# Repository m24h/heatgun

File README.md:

# heatgun
A small hot air station for soldering, using type-858 heat gun as handle, STC8G1k17 as MCU, copper wire resistor for cold junction compensation.

##Features:

* Small, cheap, esay to make
* With cold junction compensation
* Software correction 
* Compatible with most type-858 handle
* Settings can be remembered
* PID temperature control

## Burning/Downloading

This program is only for MCU STC8G1K17-16pin, compiled and linked by SDCC 4.2.0

It must be burned at following scheme:

* Internal IRC Freq. : 22.1184MHz (as same as specified in def.h)
* User EEPROM size : 2k (as same as specified in def.h)
* Low-voltage reset : Enable
* Reset pin used as I/O port : Yes
* Hardware enable WDT : Disable (I will use software enable it)
* Add a reset code in front of ID : Yes (it will adds Band-Gap voltage reference)
* Erase all EEPROM data : Yes
* Fill data to space area : 0XFF

## About cold junction compensation for the thermocouple in the handle

I add a coper wire wound resistor (nearly 13.5 OHM) in the handle, in series with the thermocouple, for cold junction compensation at a suitable bias current.
And my software will do some corrections/calculations for getting accurate temperature from the thermocouple.

But if the connector between your handle and main controller board is not in good contact, this will introduce jitter in the temperature values.

In this case, the coper wire resistor can be totally removed, and several components (R5,R13) on the PCB can also be removed,
and several parameters inside the program can also be adjusted (set g_ana_pk=0 at main.c). 

In fact, the temperature rising of the thermocouple's cold junction within the handle, is not obvious. 
It is not really necessary to do cold junction compensation, and there are already an offset compensation. 
As long as you press and hold the button at startup, you can enter room temperature parameter.
In most cases, this is enough.

## About offset adjustment for AMP (LM321)

LM321 used in my circuit is not a precision OP-AMP and there may be large input offset voltage (normally within a few millivolts).
Because of the cold junction compensation circuit, its negative offset can be ignored, 
but if the positive offset is too large, it may be necessary to add resistor (R14) to the circuit for keeping the output in the linear range.

If you remove the cold junction compensation resistor in the handle, and the negative offset cannot be ignored, 
I suggest that you still need to add one resistor in series, however, this resistor can take a larger value, 
and at the same time increase the values of R5 and R13 in the circuit, 
so that there will be no obvious jitter caused by the connector contact resistor.

Also do not adjust the offset to 0, keep an output of OP-AMP hundreds of millivolts at least.

## About the gain of AMP (LM321)

LM321 is also not a rail-to-rail OP-AMP, especially since its high output is close to 1V away from the power voltage.

If the gain designed is too large, the temperature measurement range will be limited. 
With my current design, there is no problem with the range within 500 centidegrees, 
but if a larger range is needed, the gain needs to be reduced (change R8/R9) and the parameters (g_ana_gain at main.c) in program needs to be adjusted too.

## About power supply

The circuit requires 2 ways of power supply, a 5V for controller, another 24V for the fan (normally 24V 0.1xxA) in the handle.
I didn't include this in my design, you can use the finished product from other way, or modify an unused phone charger like me (10W required).

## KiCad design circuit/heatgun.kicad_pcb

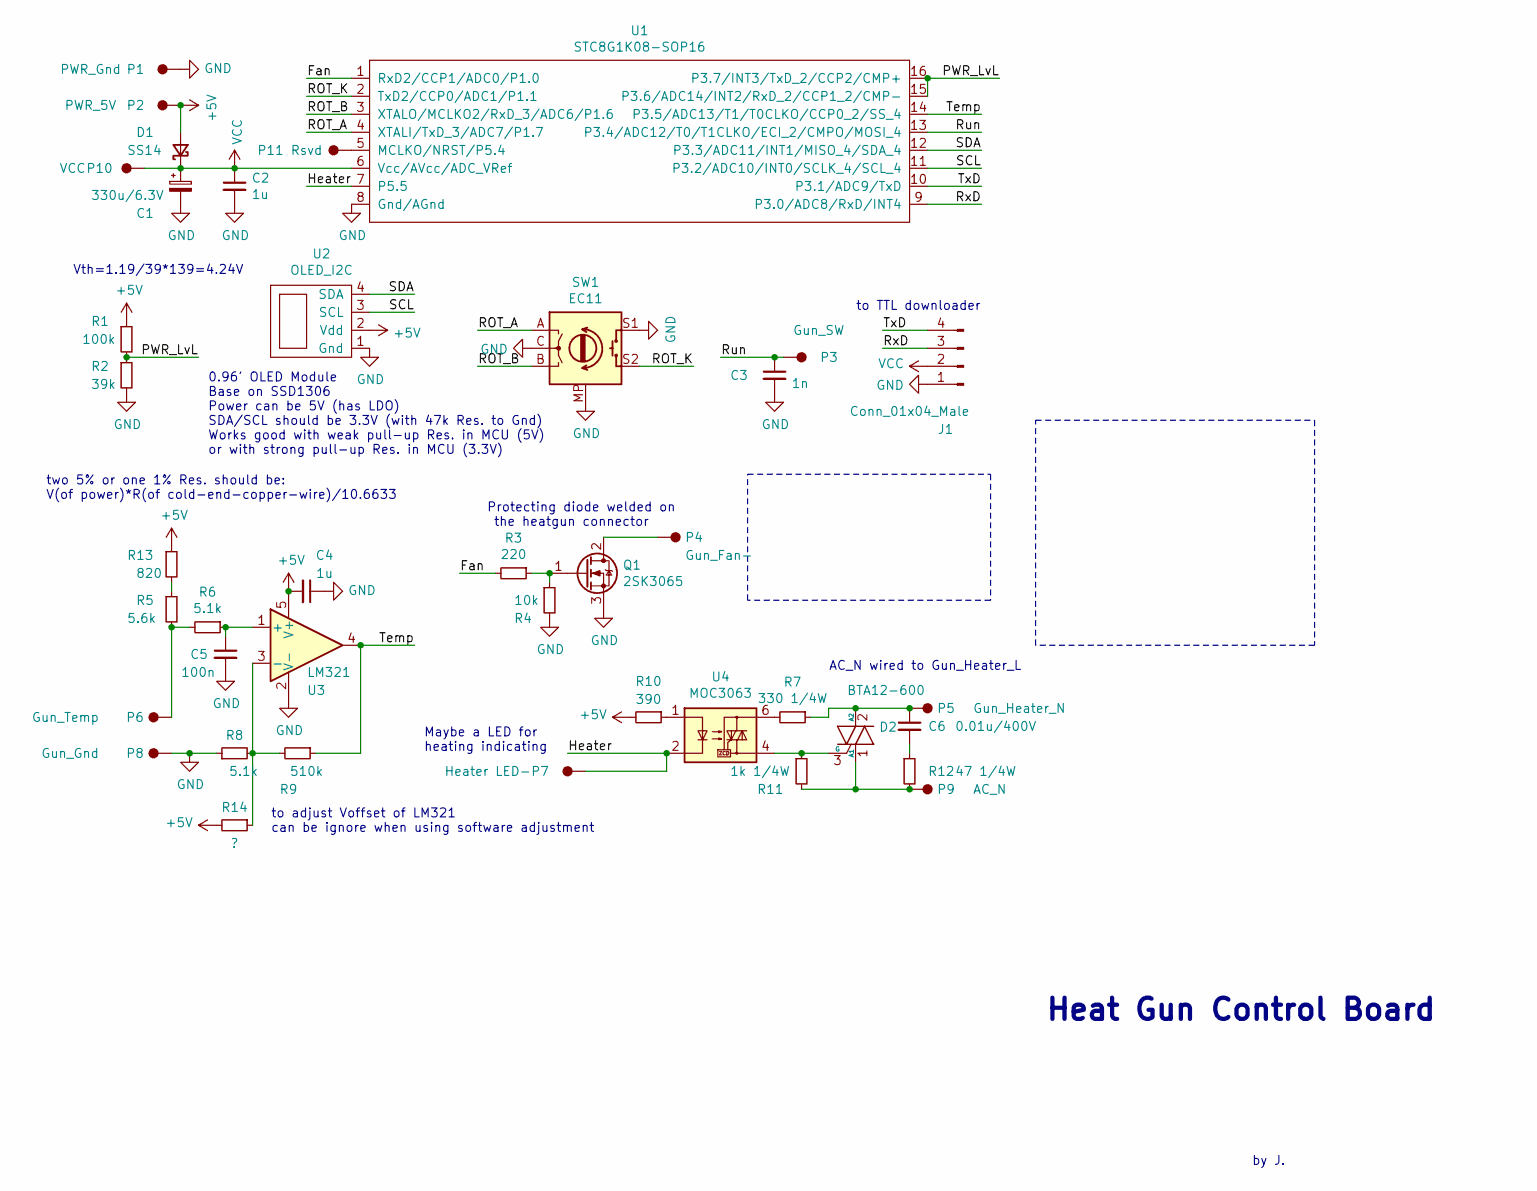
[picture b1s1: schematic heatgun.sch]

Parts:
C1: 330u/6.3V; CP_Radial_D8.0mm_P5.00mm
C2, C4: 1u; C_0603_1608Metric
C3: 1n; C_0603_1608Metric
C5: 100n; C_0603_1608Metric
C6: 0.01u/400V; C_Rect_L7.0mm_W2.5mm_P5.00mm
D1: SS14; D_SMA
D2: BTA12-600; TO-220-3_Vertical
J1: Conn_01x04_Male; PinHeader_1x04_P2.54mm_Vertical
P1: PWR_Gnd; Pad-1.8-h1
P2: PWR_5V; Pad-1.8-h1
P3: Gun_SW; Pad-1.8-h1
P4: Gun_Fan-; Pad-1.8-h1
P5: Gun_Heater_N; Pad-2.5-h1
P6: Gun_Temp; Pad-1.8-h1
P7: Heater LED-; Pad-1.8-h1
P8: Gun_Gnd; Pad-1.8-h1
P9: AC_N; Pad-2.5-h1
P10: VCC; Pad-1.8-h1
P11: Rsvd; Pad-1.8-h1
Q1: 2SK3065; SOT-89-3
R1: 100k; R_0603_1608Metric
R2: 39k; R_0603_1608Metric
R3: 220; R_0603_1608Metric
R4: 10k; R_0603_1608Metric
R5: 5.6k; R_0603_1608Metric
R6, R8: 5.1k; R_0603_1608Metric
R7: 330 1/4W; R_Axial_DIN0207_L6.3mm_D2.5mm_P10.16mm_Horizontal
R9: 510k; R_0603_1608Metric
R10: 390; R_Axial_DIN0207_L6.3mm_D2.5mm_P10.16mm_Horizontal
R11: 1k 1/4W; R_Axial_DIN0207_L6.3mm_D2.5mm_P10.16mm_Horizontal
R12: 47 1/4W; R_Axial_DIN0207_L6.3mm_D2.5mm_P10.16mm_Horizontal
R13: 820; R_0603_1608Metric
R14: ?; R_0603_1608Metric
SW1: EC11; RotaryEncoder_Alps_EC11E-Switch_Vertical_H20mm
U1: STC8G1K08-SOP16; SOIC-16_3.9x9.9mm_P1.27mm
U2: OLED_I2C; OLED-I2C-0.96-27.5X27.8
U3: LM321; SOT-23-5
U4: MOC3063; DIP-6_W7.62mm

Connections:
+5V: C4.2, D1.2 (A), P2.1, R1.1, R10.2, R13.1, R14.2, U2.2 (Vdd), U3.5 (V+)
/Fan: R3.2, U1.1 (RxD2/CCP1/ADC0/P1.0)
/Heater: P7.1, U1.7 (P5.5), U4.2
/PWR_LvL: R1.2, R2.1, U1.15 (P3.6/ADC14/INT2/RxD_2/CCP1_2/CMP-), U1.16 (P3.7/INT3/TxD_2/CCP2/CMP+)
/ROT_A: SW1.A, U1.4 (XTALI/TxD_3/ADC7/P1.7)
/ROT_B: SW1.B, U1.3 (XTALO/MCLKO2/RxD_3/ADC6/P1.6)
/ROT_K: SW1.S2, U1.2 (TxD2/CCP0/ADC1/P1.1)
/Run: C3.1, P3.1, U1.13 (P3.4/ADC12/T0/T1CLKO/ECI_2/CMPO/MOSI_4)
/RxD: J1.3, U1.9 (P3.0/ADC8/RxD/INT4)
/SCL: U1.11 (P3.2/ADC10/INT0/SCLK_4/SCL_4), U2.3 (SCL)
/SDA: U1.12 (P3.3/ADC11/INT1/MISO_4/SDA_4), U2.4 (SDA)
/Temp: R9.1, U1.14 (P3.5/ADC13/T1/T0CLKO/CCP0_2/SS_4), U3.4
/TxD: J1.4, U1.10 (P3.1/ADC9/TxD)
GND: C1.2, C2.2, C3.2, C4.1, C5.2, J1.1, P1.1, P8.1, Q1.3 (S), R2.2, R4.2, R8.1, SW1.C, SW1.MP, SW1.S1, U1.8 (Gnd/AGnd), U2.1 (Gnd), U3.2 (V-)
unnamed: C5.1, R6.1, U3.1 (+)
unnamed: C6.1, D2.2 (A2), P5.1, R7.1
unnamed: C6.2, R12.1
unnamed: D2.1 (A1), P9.1, R11.2, R12.2
unnamed: D2.3 (G), R11.1, U4.4
unnamed: P4.1, Q1.2 (D)
unnamed: P6.1, R5.2, R6.2
unnamed: P11.1, U1.5 (MCLKO/NRST/P5.4)
unnamed: Q1.1 (G), R3.1, R4.1
unnamed: R7.2, U4.6
unnamed: R10.1, U4.1
unnamed: R5.1, R13.2
unnamed: R8.2, R9.2, R14.1, U3.3 (-)
VCC: C1.1, C2.1, D1.1 (K), J1.2, P10.1, U1.6 (Vcc/AVcc/ADC_VRef)

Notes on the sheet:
Protecting diode welded on the heatgun connector
AC_N wired to Gun_Heater_L
to TTL downloader
0.96' OLED Module Base on SSD1306 Power can be 5V (has LDO) SDA/SCL should be 3.3V (with 47k Res. to Gnd) Works good with weak pull-up Res. in MCU (5V) or with strong pull-up Res. in MCU (3.3V)
Maybe a LED for heating indicating
Vth=1.19/39*139=4.24V
two 5% or one 1% Res. should be: V(of power)*R(of cold-end-copper-wire)/10.6633
to adjust Voffset of LM321 can be ignore when using software adjustment
Heat Gun Control Board
by J.

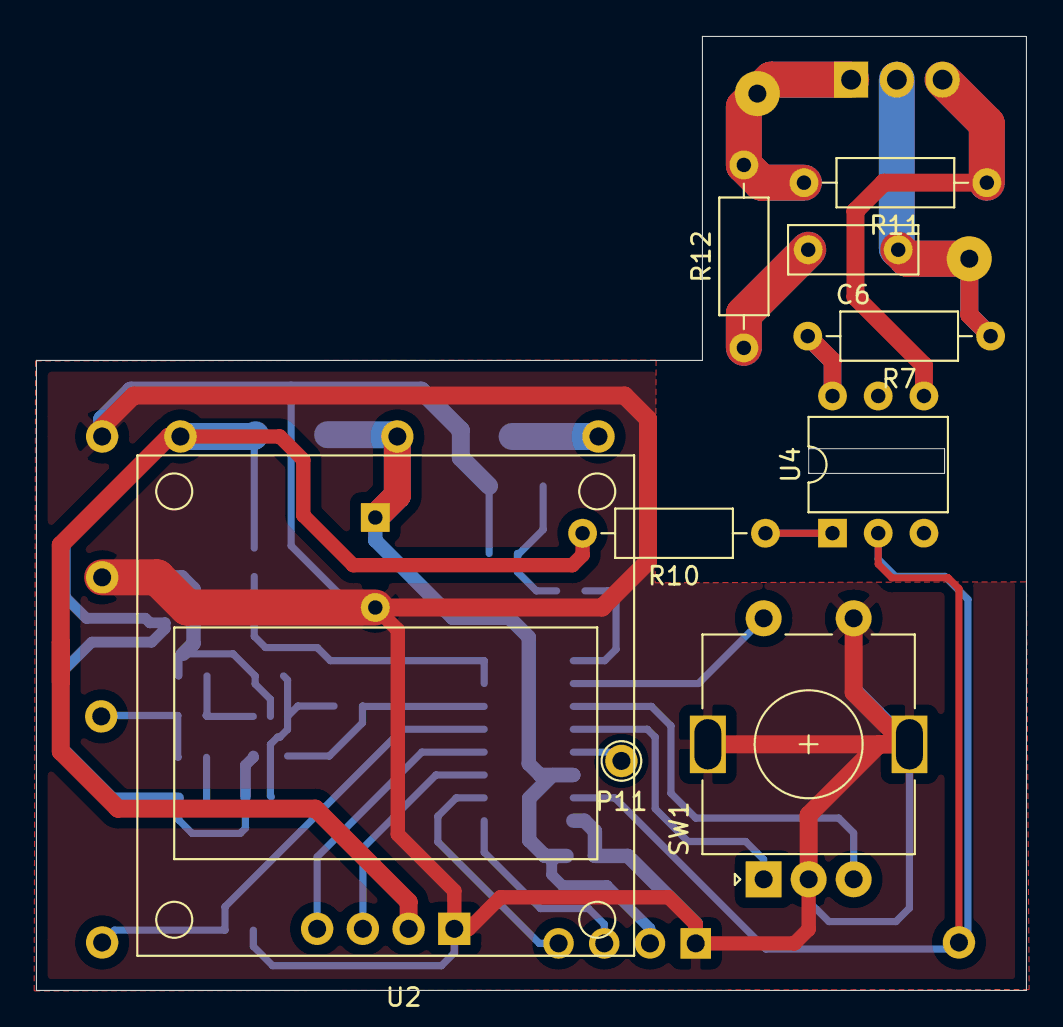
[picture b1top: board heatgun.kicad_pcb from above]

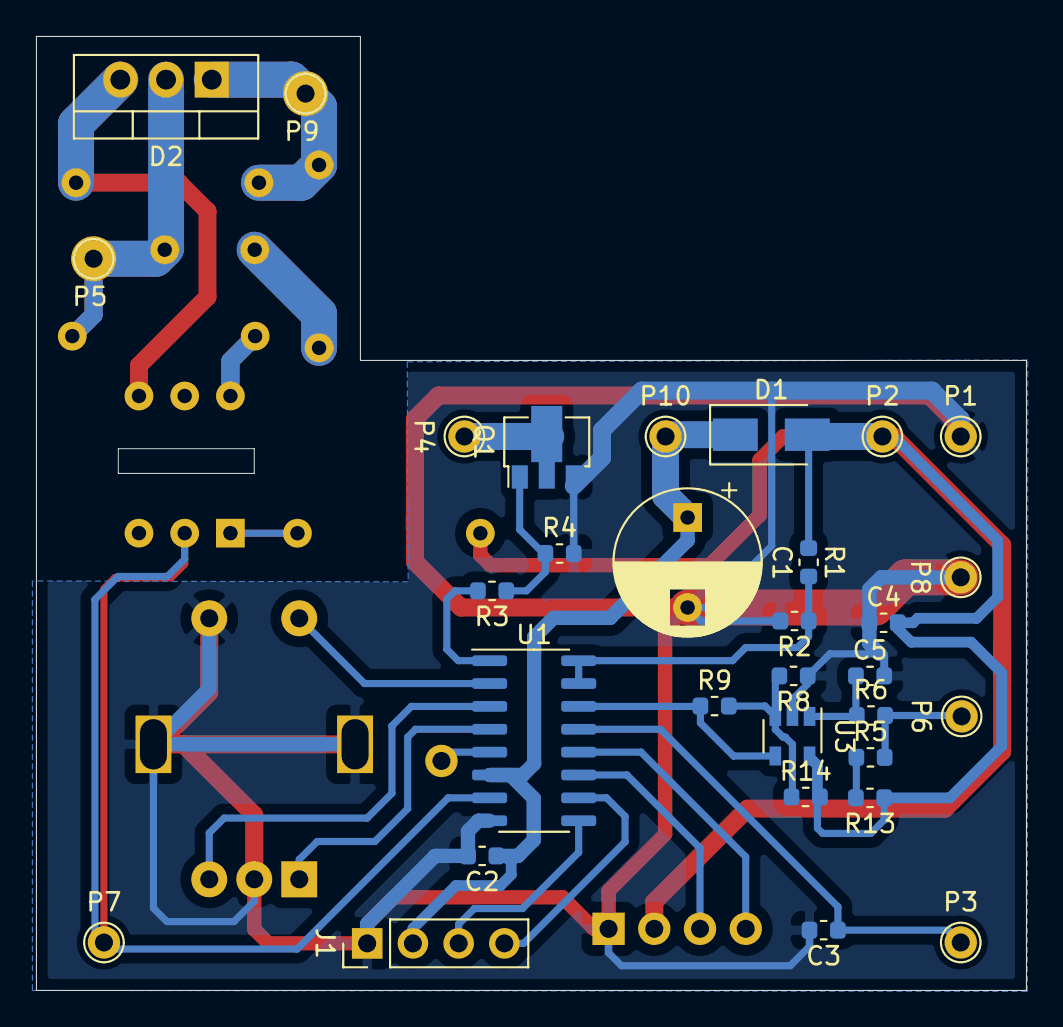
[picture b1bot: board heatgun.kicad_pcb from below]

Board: 2 copper layers, 55.0 x 53.0 mm, 40 parts (31 on the bottom side), 28 nets.

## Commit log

2023-02-09 First commit Signed-off-by: m24h <jjkkxyz@hotmail.com>
2023-02-09 Add compiler/linker information Signed-off-by: m24h <jjkkxyz@hotmail.com>
